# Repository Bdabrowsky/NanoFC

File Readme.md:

# Hardware files for Open Source flight computer
## For software, visit [Source Page](https://github.com/Bdabrowsky/Clockwork_Orange)
## All above hardware is made using funding from [Odkrywcy Diamentów](https://odkrywcydiamentow.com.pl/) grant program

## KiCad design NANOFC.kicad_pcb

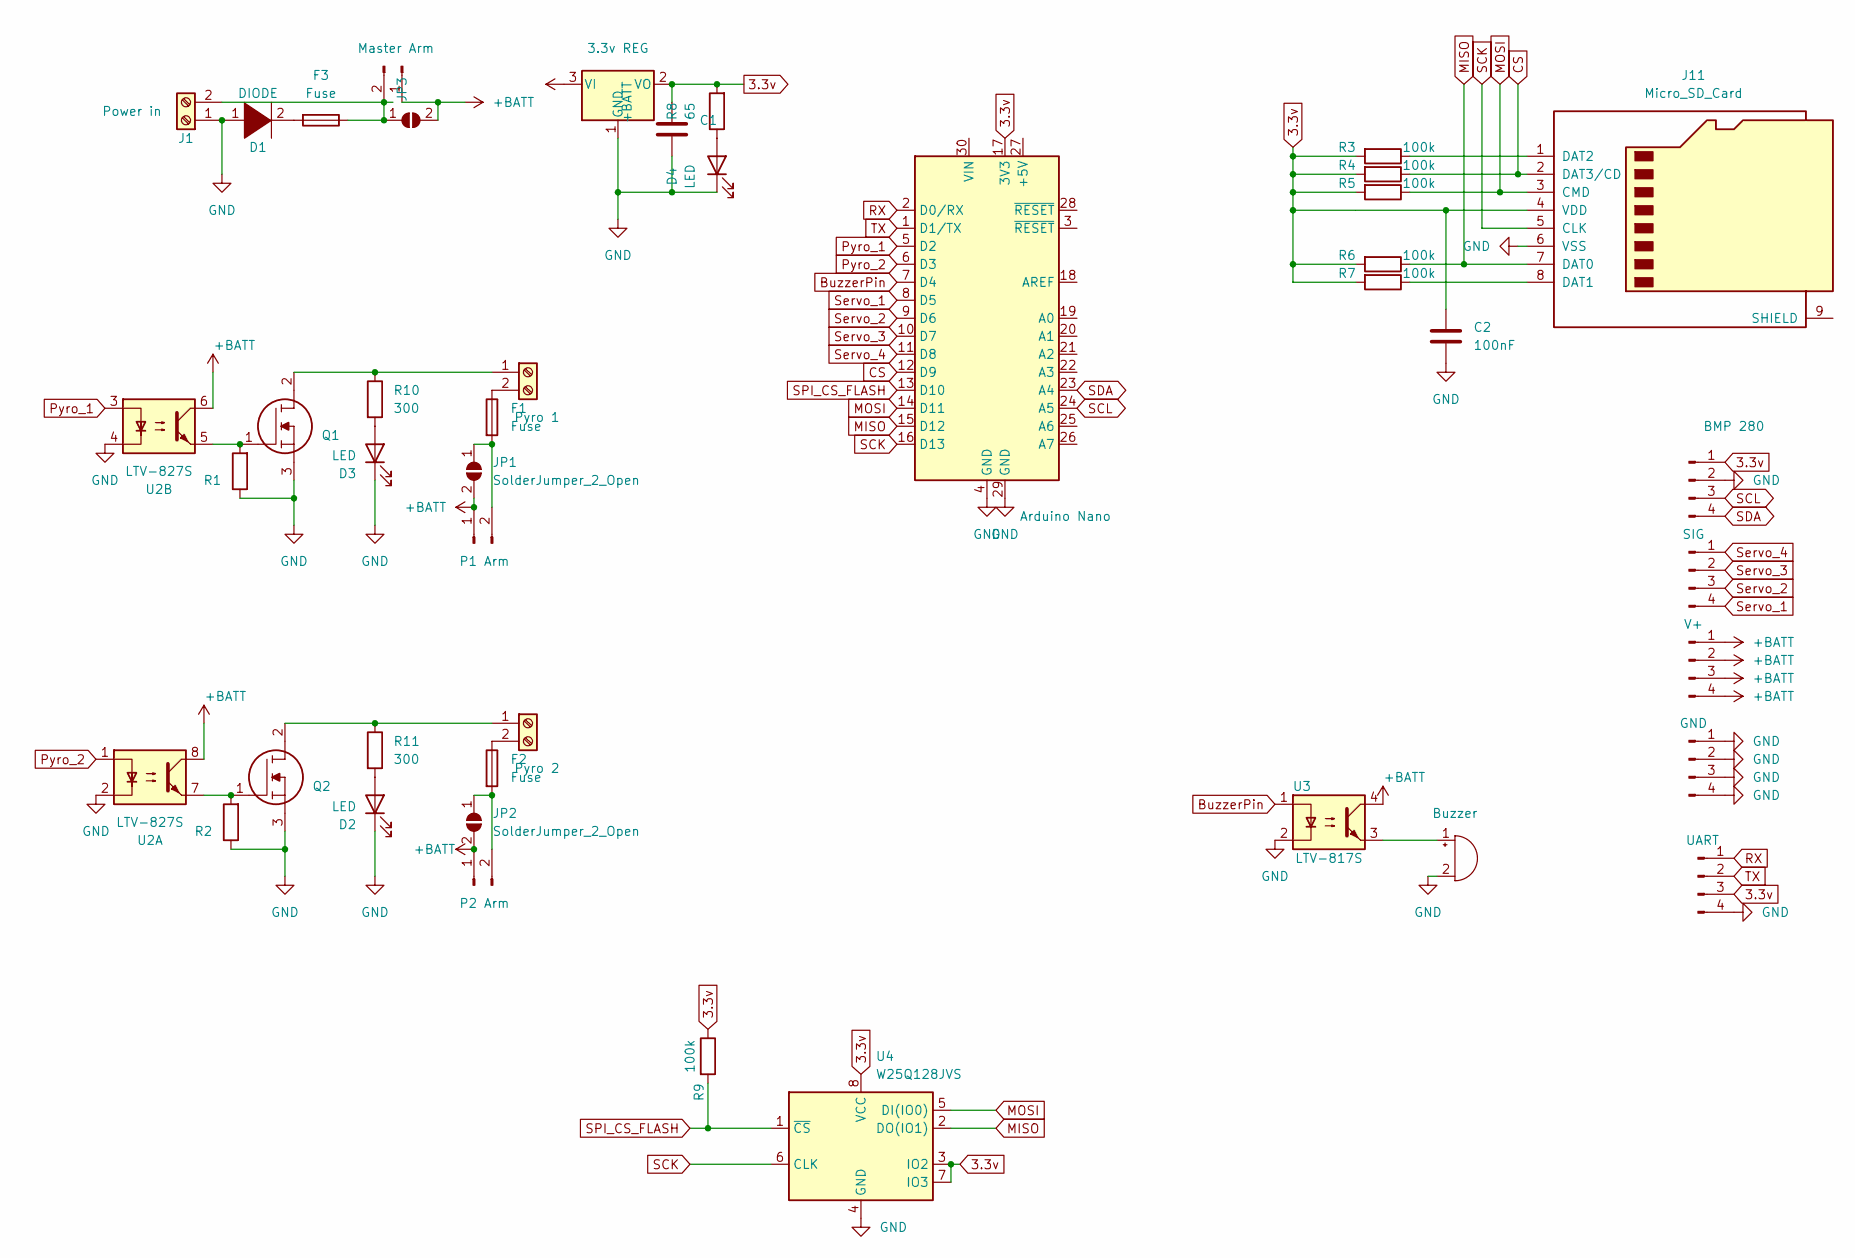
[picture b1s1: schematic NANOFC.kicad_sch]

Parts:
A1: Arduino Nano; Arduino_Nano
BZ1: Buzzer; Buzzer_CUI_CPT-9019S-SMT
C1: 100nf; C_1210_3225Metric
C2: 100nF; C_1210_3225Metric
D1: DIODE; D_1210_3225Metric
D2, D3, D4: LED; LED_PLCC-2
F1, F2, F3: Fuse; Fuse_1206_3216Metric
J1: Power in; TerminalBlock_4Ucon_1x02_P3.50mm_Vertical
J2: Pyro 1; TerminalBlock_4Ucon_1x02_P3.50mm_Vertical
J3: BMP 280; PinHeader_1x04_P2.54mm_Vertical
J4: Pyro 2; TerminalBlock_4Ucon_1x02_P3.50mm_Vertical
J5: SIG; PinHeader_1x04_P2.54mm_Vertical
J6: V+; PinHeader_1x04_P2.54mm_Vertical
J7: GND; PinHeader_1x04_P2.54mm_Vertical
J8: Master Arm; PinHeader_1x02_P2.54mm_Vertical
J9: P1 Arm; PinHeader_1x02_P2.54mm_Vertical
J10: P2 Arm; PinHeader_1x02_P2.54mm_Vertical
J11: Micro_SD_Card; microSD_HC_Hirose_DM3D-SF
J12: UART; JST_EH_B4B-EH-A_1x04_P2.50mm_Vertical
JP1, JP2, JP3: SolderJumper_2_Open; SolderJumper-2_P1.3mm_Open_Pad1.0x1.5mm
Q1, Q2: IRLR2905TRPBF; TO-252-2; Manufacturer_Part_Number IRLR2905TRPBF; Mouser Part Number 942-IRLR2905TRPBF
R1, R2: 10k; R_1210_3225Metric
R3, R4, R5, R6, R7, R9: 100k; R_1210_3225Metric
R8: 65; LED_1210_3225Metric
R10, R11: 300; R_1210_3225Metric
U1: 3.3v REG; SOT-223-3_TabPin2
U2: LTV-827S; SMDIP-8_W9.53mm
U3: LTV-817S; SMDIP-4_W9.53mm
U4: W25Q128JVS; SON127P500X600X80-9N

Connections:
3.3v: A1.17 (3V3), C1.1, J3.1, J12.3, R3.2, R4.2, R5.2, R6.2, R7.2, R8.2, R9.1, U1.2 (VO), U4.3 (IO2), U4.7 (IO3), U4.8 (VCC)
+BATT: J6.1, J6.2, J6.3, J6.4, J8.1, J9.1, J10.1, JP1.2 (B), JP2.2 (B), JP3.2 (B), U1.3 (VI), U2.6, U2.8, U3.4
BuzzerPin: A1.7 (D4), U3.1
CS: A1.12 (D9), J11.2 (DAT3/CD), R4.1
GND: A1.4 (GND), A1.29 (GND), BZ1.2 (+), C1.2, C2.2, D1.1 (K), D2.1 (K), D3.1 (K), D4.1 (K), J1.1, J3.2, J7.1, J7.2, J7.3, J7.4, J11.6 (VSS), J12.4, Q1.3, Q2.3, R1.1, R2.1, U1.1 (GND), U2.2, U2.4, U3.2, U4.4 (GND)
MISO: A1.15 (D12), J11.7 (DAT0), R6.1, U4.2 (DO(IO1))
MOSI: A1.14 (D11), J11.3 (CMD), R5.1, U4.5 (DI(IO0))
unnamed: BZ1.1 (-), U3.3
unnamed: C2.1, J11.4 (VDD)
unnamed: D1.2 (A), F3.2
unnamed: D2.2 (A), R11.2
unnamed: F1.1, J2.2
unnamed: F1.2, J9.2, JP1.1 (A)
unnamed: F2.1, J4.2
unnamed: F2.2, J10.2, JP2.1 (A)
unnamed: F3.1, J1.2, J8.2, JP3.1 (A)
unnamed: J2.1, Q1.2, R10.1
unnamed: J4.1, Q2.2, R11.1
unnamed: J11.1 (DAT2), R3.1
unnamed: J11.8 (DAT1), R7.1
unnamed: Q1.1, R1.2, U2.5
unnamed: Q2.1, R2.2, U2.7
unnamed: D4.2 (A), R8.1
unnamed: D3.2 (A), R10.2
Pyro_1: A1.5 (D2), U2.3
Pyro_2: A1.6 (D3), U2.1
RX: A1.2 (D0/RX), J12.1
SCK: A1.16 (D13), J11.5 (CLK), U4.6 (CLK)
SCL: A1.24 (A5), J3.3
SDA: A1.23 (A4), J3.4
SPI_CS_FLASH: A1.13 (D10), R9.2, U4.1 (~CS)
Servo_1: A1.8 (D5), J5.4
Servo_2: A1.9 (D6), J5.3
Servo_3: A1.10 (D7), J5.2
Servo_4: A1.11 (D8), J5.1
TX: A1.1 (D1/TX), J12.2

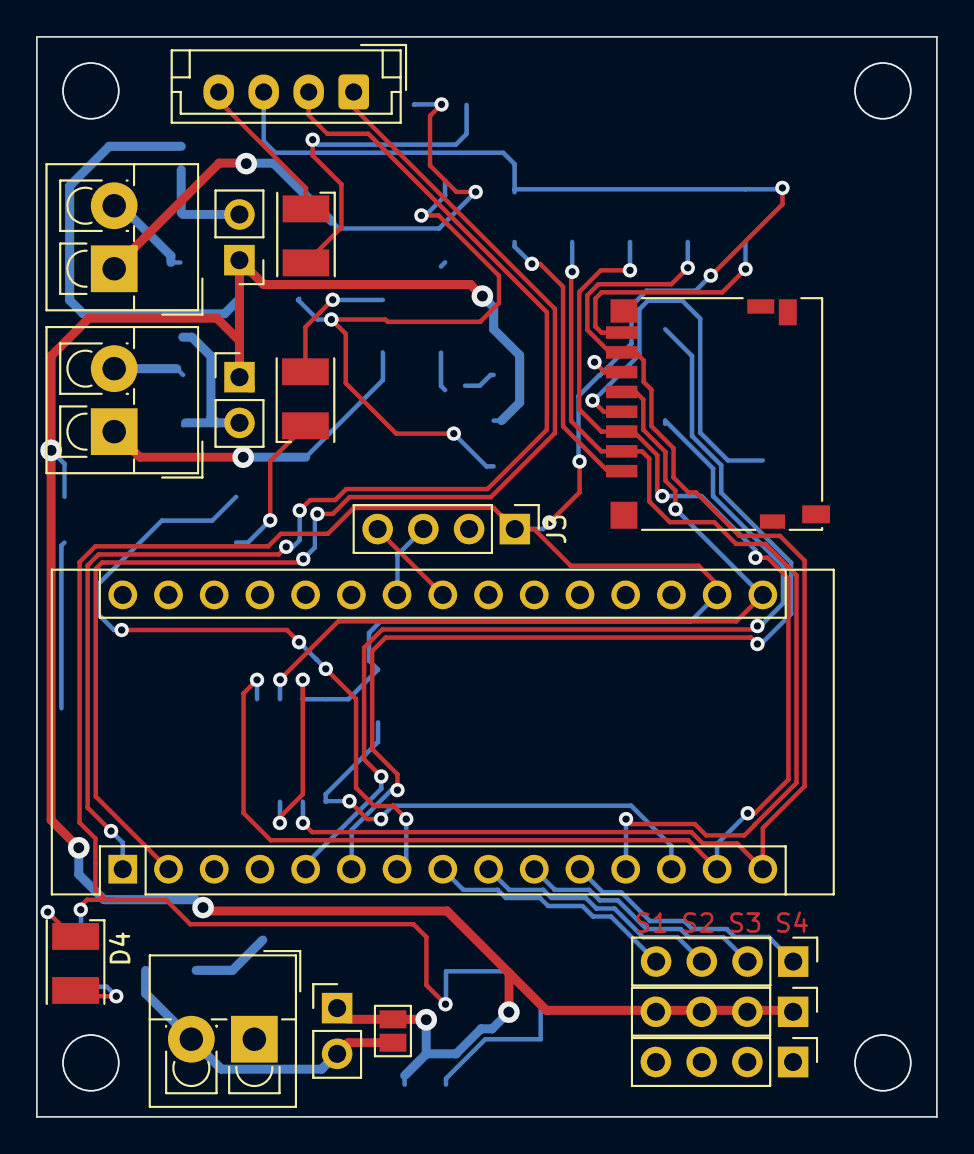
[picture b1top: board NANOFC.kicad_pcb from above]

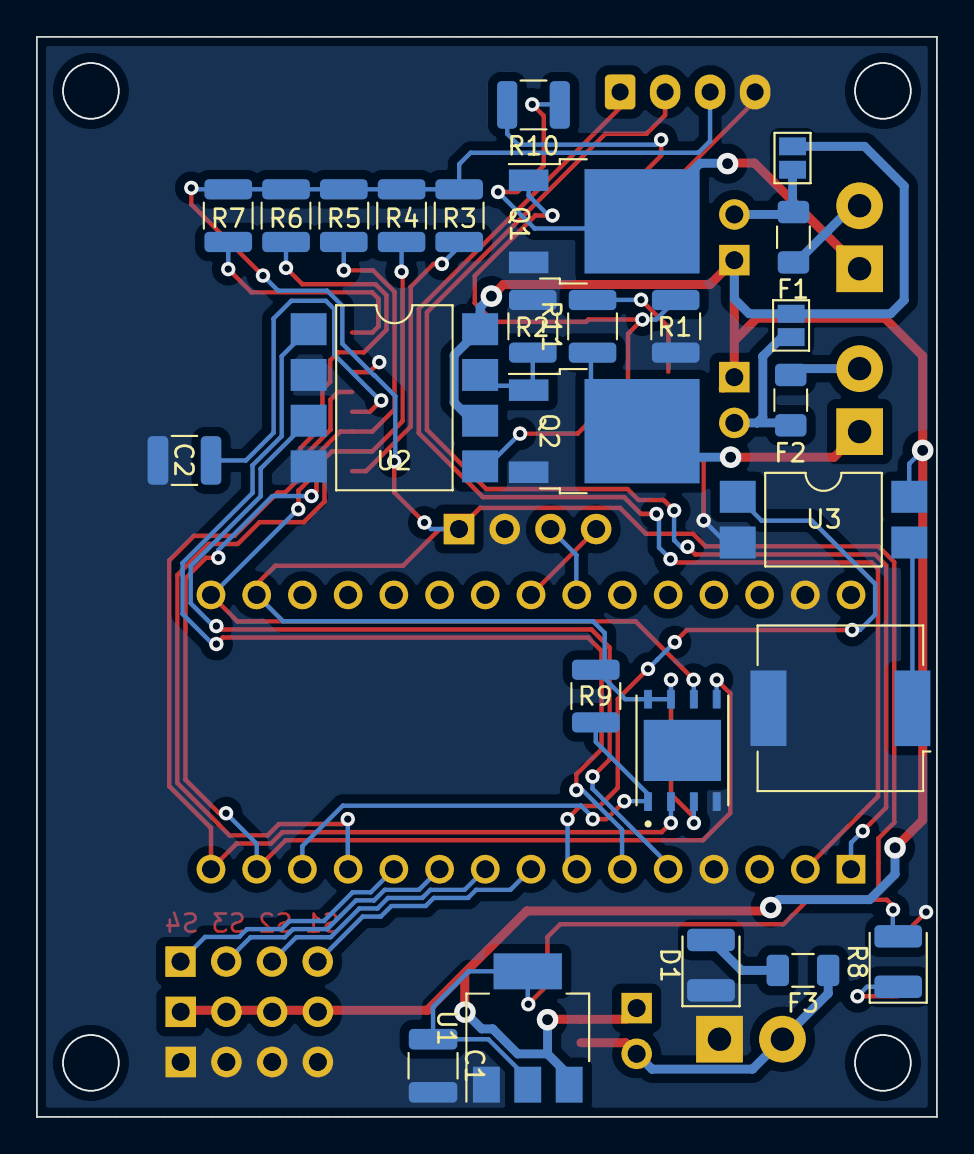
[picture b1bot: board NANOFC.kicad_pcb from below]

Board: 2 copper layers, 50.0 x 60.0 mm, 43 parts (26 on the bottom side), 36 nets.

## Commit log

2022-06-11 0.0.0.0
2022-06-28 clear
2022-08-06 Fix
    Fixed:
    pyro channels
    Added:
    status leds
    continuity test leds
    breakers
2022-08-10 v2.1
2022-09-25 Create LICENSE
